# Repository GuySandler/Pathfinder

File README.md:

# Pathfinder

I made 2 different game firmwares for this to pass time.

There is not a lot I can do with 4 LEDs and 4 Buttons

## Board Images

### PCB Design

### Schematic

### Assembled Board

## Games

### Memory Game
Starts with 1 and goes up every time you get it correct up to 50 (good luck). Has win, loose, and start animations.

### Whack-a-Mole
Press the buttons with the LEDs as they light up before they go away to score points. Has win and start animations along with showing your score at the end by 4ths (12, 25, 35, 50)

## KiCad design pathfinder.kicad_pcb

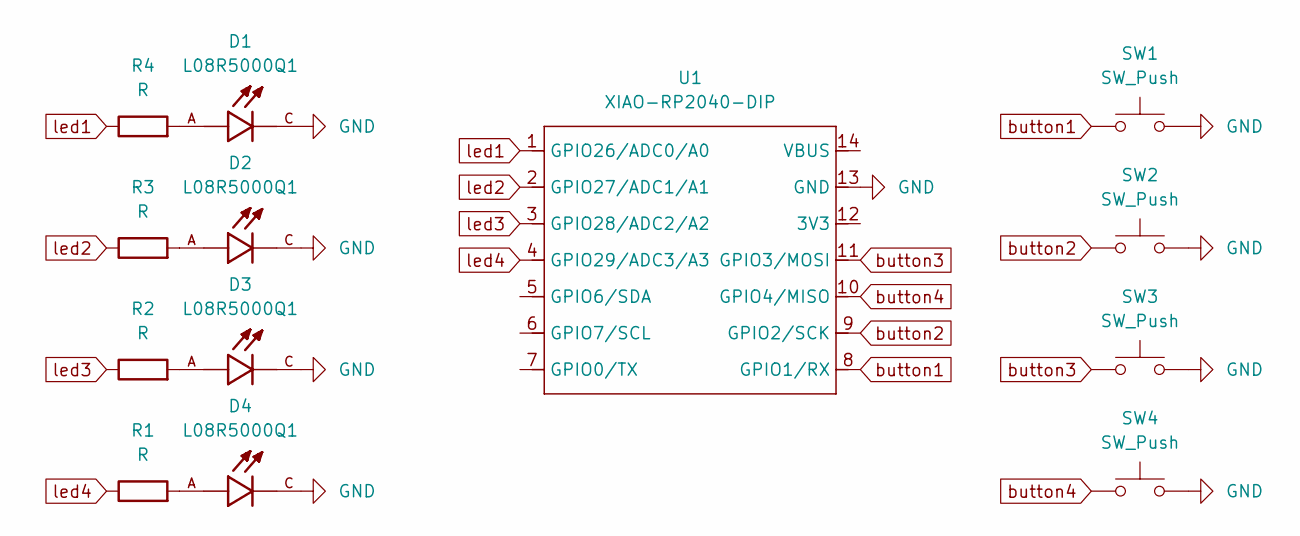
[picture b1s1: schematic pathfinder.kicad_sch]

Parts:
D1, D2, D3, D4: L08R5000Q1; LEDRD254W57D500H1070; PARTREV NA
R1, R2, R3, R4: R; R_Axial_DIN0204_L3.6mm_D1.6mm_P5.08mm_Horizontal
SW1, SW2, SW3, SW4: SW_Push; SW_Cherry_MX_1.00u_PCB
U1: XIAO-RP2040-DIP

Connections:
GND: D1.C, D2.C, D3.C, D4.C, SW1.2, SW2.2, SW3.2, SW4.2, U1.13 (GND)
unnamed: D1.A, R4.2
unnamed: D2.A, R3.2
unnamed: D3.A, R2.2
unnamed: D4.A, R1.2
button1: SW1.1, U1.8 (GPIO1/RX)
button2: SW2.1, U1.9 (GPIO2/SCK)
button3: SW3.1, U1.11 (GPIO3/MOSI)
button4: SW4.1, U1.10 (GPIO4/MISO)
led1: R4.1, U1.1 (GPIO26/ADC0/A0)
led2: R3.1, U1.2 (GPIO27/ADC1/A1)
led3: R2.1, U1.3 (GPIO28/ADC2/A2)
led4: R1.1, U1.4 (GPIO29/ADC3/A3)

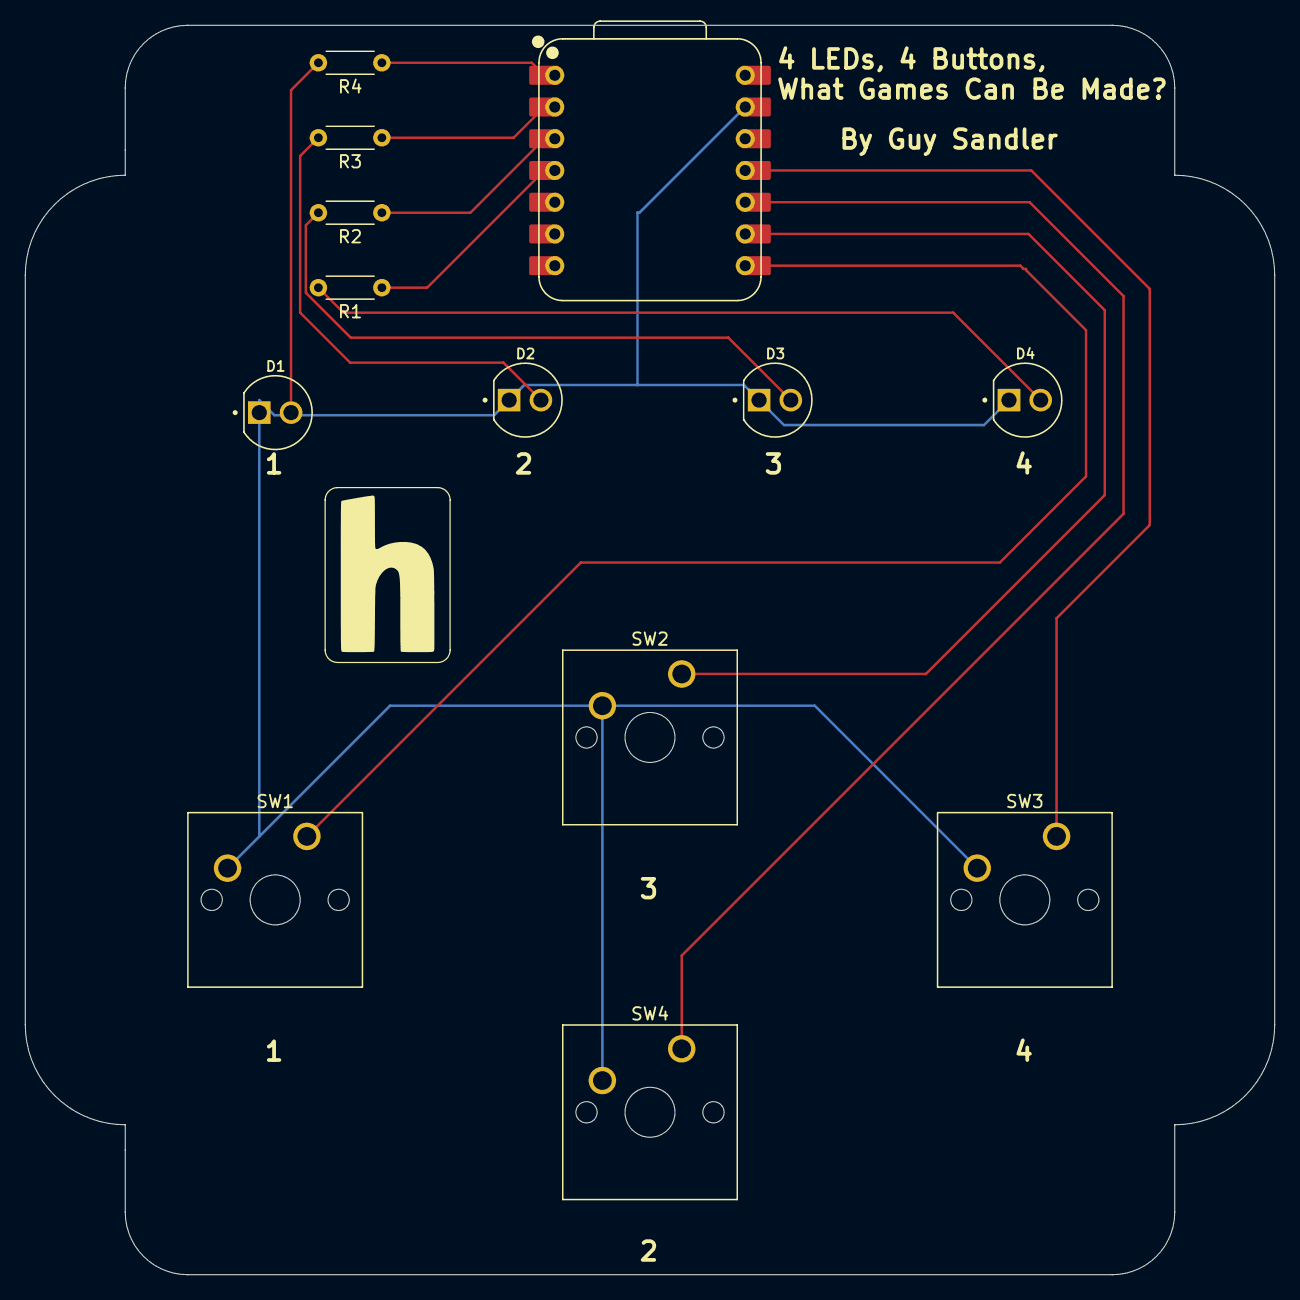
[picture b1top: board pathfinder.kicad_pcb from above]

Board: 2 copper layers, 100.0 x 100.0 mm, 14 parts (0 on the bottom side), 13 nets.

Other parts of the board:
 : LOGO

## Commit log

2025-07-03 firmware done
2025-07-04 redid pcb style and added another game
2025-07-04 fixed readme
2025-07-04 quick script fix
